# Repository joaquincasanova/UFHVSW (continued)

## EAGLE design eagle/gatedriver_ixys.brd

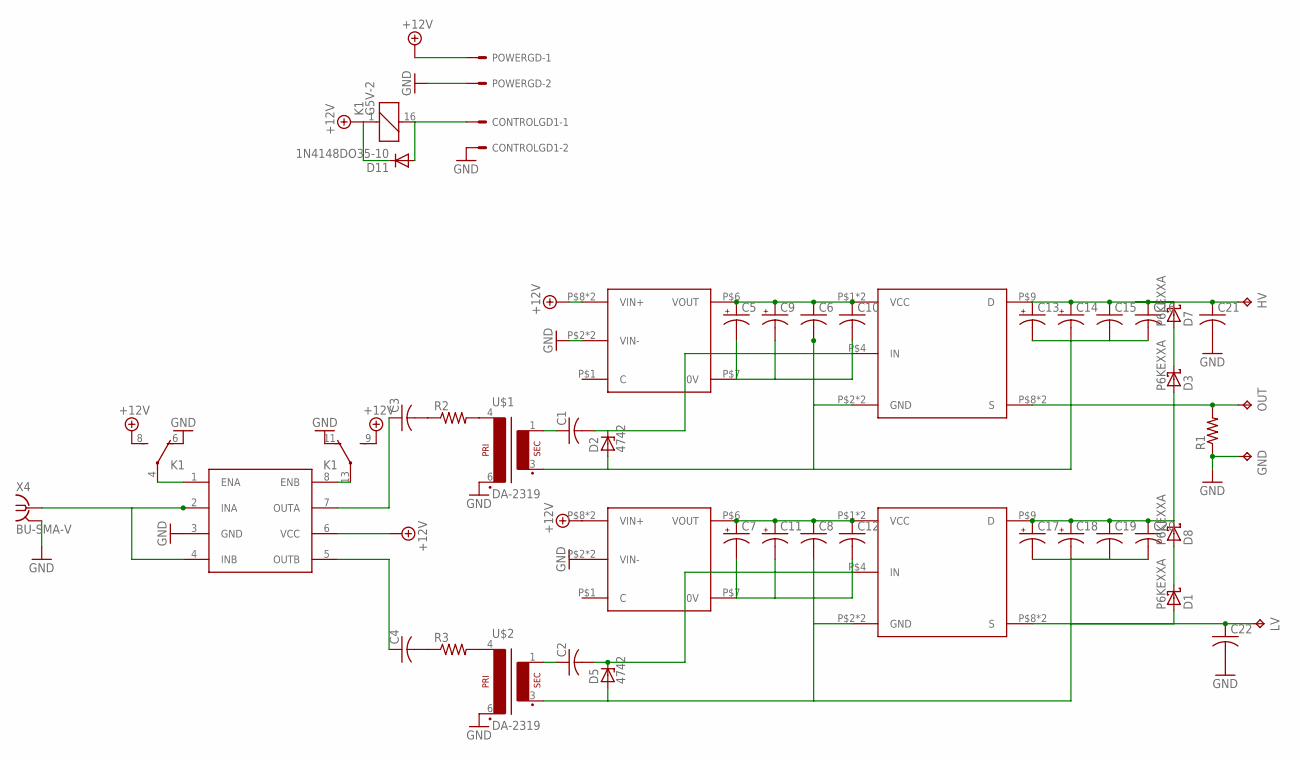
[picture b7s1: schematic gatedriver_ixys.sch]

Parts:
C1, C2, C3, C4: C-US050-055X075; C050-055X075
C5, C7, C9, C11, C13, C14, C17, C18: CPOL-USE5-10.5; E5-10,5
C6, C8, C10, C12, C15, C16, C19, C20: C-US050-075X075; C050-075X075
C21, C22: C-US102-064X133; C102-064X133
CONTROLGD1: KK-156-2
D1, D3, D7, D8: P6KEXXA; C1702-15
D2, D5: 4742; ZDIO-10
D11: 1N4148DO35-10; DO35-10
DC1, DC2: NCS
GND: TPPAD1-20Y; P1-20Y
HV: TPPAD1-20Y; P1-20Y
K1: G5V-2
LV: TPPAD1-20Y; P1-20Y
OUT: TPPAD1-20Y; P1-20Y
POWERGD: KK-156-2
R1: R-US_0414/15; 0414/15
R2: R-US_0207/15; 0207/15
R3: R-US_0207/12; 0207/12
U$1, U$2: DA-2319; DIL06
U$3: UCC27425; DIL08
U$8, U$9: IXZ631DF12N100
X4: BU-SMA-V

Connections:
+12V: D11.C, DC1.P$8 (VIN+), DC1.P$9 (VIN+), DC2.P$8 (VIN+), DC2.P$9 (VIN+), K1.1, K1.8 (S), K1.9 (S), POWERGD.1, U$3.6 (VCC)
ENSW: CONTROLGD1.1, D11.A, K1.16 (2)
GND: C21.2, C22.2, CONTROLGD1.2, DC1.P$2 (VIN-), DC1.P$3 (VIN-), DC2.P$2 (VIN-), DC2.P$3 (VIN-), GND.TP, K1.6 (O), K1.11 (O), POWERGD.2, R1.1, U$1.6 (P2), U$2.6 (P2), U$3.3 (GND), X4.2, X4.3 (2), X4.4 (2), X4.5 (2)
unnamed: U$3.2 (INA), U$3.4 (INB), X4.1
unnamed: C3.1, U$3.7 (OUTA)
unnamed: R2.2, U$1.4 (P1)
unnamed: C4.1, U$3.5 (OUTB)
unnamed: R3.2, U$2.4 (P1)
unnamed: C4.2, R3.1
unnamed: C5.+, C6.1, C9.+, C10.1, DC1.P$6 (VOUT), U$8.P$1 (VCC), U$8.P$7 (VCC)
unnamed: C7.+, C8.1, C11.+, C12.1, DC2.P$6 (VOUT), U$9.P$1 (VCC), U$9.P$7 (VCC)
unnamed: D3.C, D7.A
unnamed: C1.1, U$1.1 (S4)
unnamed: C2.1, U$2.1 (S4)
unnamed: C1.2, D2.C, U$8.P$4 (IN)
unnamed: K1.4, U$3.1 (ENA)
unnamed: K1.13, U$3.8 (ENB)
unnamed: C3.2, R2.1
unnamed: C13.+, C14.+, C15.1, C16.1, C21.1, D7.C, HV.TP, U$8.P$9 (D)
unnamed: D1.C, D8.A
unnamed: C7.-, C8.2, C11.-, C12.2, C17.-, C18.-, C19.2, C20.2, C22.1, D1.A, D5.A, DC2.P$7 (0V), LV.TP, U$2.3 (S3), U$9.P$2 (GND), U$9.P$6 (GND), U$9.P$8 (S), U$9.P$10 (S)
unnamed: C5.-, C6.2, C9.-, C10.2, C13.-, C14.-, C15.2, C16.2, C17.+, C18.+, C19.1, C20.1, D2.A, D3.A, D8.C, DC1.P$7 (0V), OUT.TP, R1.2, U$1.3 (S3), U$8.P$2 (GND), U$8.P$6 (GND), U$8.P$8 (S), U$8.P$10 (S), U$9.P$9 (D)
unnamed: C2.2, D5.C, U$9.P$4 (IN)

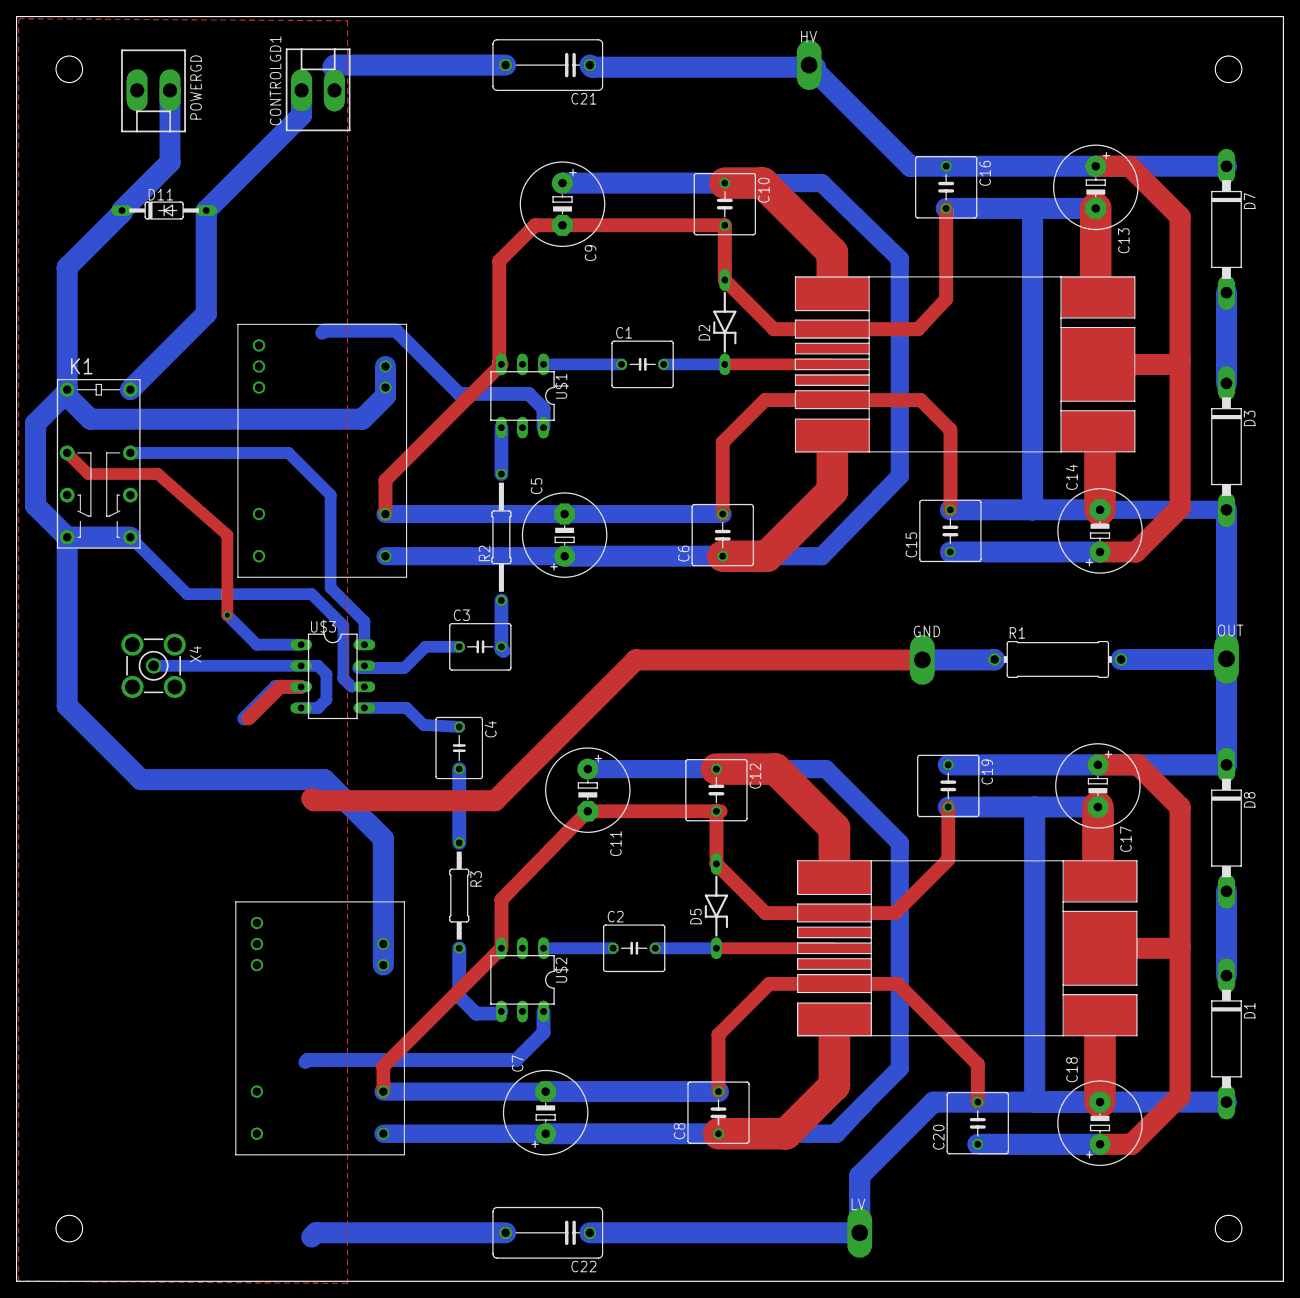
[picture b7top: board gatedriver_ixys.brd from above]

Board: 2 copper layers, 152.7 x 152.4 mm, 47 parts (0 on the bottom side), 23 nets.
